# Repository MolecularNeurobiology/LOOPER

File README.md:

# LOOPER
Live Observation and Operation of Physiology Experiments with Robotics

# What is it?
LOOPER is an automated data collection platform for neonate pneumotachography experiments focused on the Autoresuscitation Reflex Assay. Its software is written in Python, and Arduino code (C++). The robotics includes commonly available electrical components, sensors, motors, and mechanical linkages. Structural components also include extruded aluminum pieces, 3D printed pieces, and milled acrylic. Physiology signals from laboratory grade sensors are captured using a LabJack analog to digital USB capture card connected to a Raspberry Pi Single Board Computer which provides access to the user interface. An Arduino Mega microcontroller with a custom assembled printed circuit board coordinates control of motorized parts.

Tools to aid in analysis of data collected with LOOPER are co-released at https://github.com/MolecularNeurobiology/Breathe_Easy

## What is the Autoresuscitation Reflex Assay? Why is it important?
The prevailing mechanistic hypothesis of Sudden Infant Death Syndrome/Sudden Unexpected Infant Death (SIDS/SUID) is that infants experience two critical failures that lead to death. The first is a failure of arousal. Many SIDS/SUID infants are found in an unsafe sleep environment, resulting in rebreathing increasingly hypoxic and hypercapnic air. Healthy infants arouse; however, in a vulnerable infant, the rebreathing continues, resulting in increasing levels of hypoxia and hypercapnia, leading to apnea and bradycardia. As a last line of defense, the infant initiates the **autoresuscitation reflex**. It is hypothesized that this second failure in the autoresuscitation reflex is a common mechanistic pathway for many SIDS cases. 

The neonatal mouse offers a powerful model for understanding intrinsic and extrinsic risk factors that may lead to failed autoresuscitation. Mouse neonate autoresuscitation parallels human cardiorespiratory physiology and can be readily assessed by subjecting a postnatal day 7-8 (P7-8) mouse to an anoxic gas mixture (3% CO2/97% N2) until apnea and bradycardia occur. Upon apnea, the neonate is returned to room air (approximately 21% O2/79%N2) to facilitate the autoresuscitation reflex and restore cardiorespiratory function. After a short recovery period, this sequence of events is repeated either for a predetermined number of trials or until the animal succumbs. 

However, the conventional autoresuscitation assay has several limitations that preclude wider use. First, the observer must be attentive throughout the assay to watch the cardiorespiratory traces in real-time, detect apnea, and provide room air rescue gas. This requirement for manual detection of cardiorespiratory signatures leads to inconsistency and inaccuracy. Second, an observer with one apparatus (pneumotachograph) can assay about three mice daily (~2.5 hours per assay). Given that mice must be P7-8, each litter is about eight pups, and each mating pair drops a litter once a month, it is impossible to record all mice, and there is a month’s downtime between experimental days. Ultimately, this culminates in wasted time and mice. Lastly, hand annotation and quantification of the data remain the standard in the field, creating an additional workload with the potential for observer bias. Altogether, these shortcomings create a high workload, low efficiency, and the potential for variability, severely limiting one of the most powerful assays for understanding SIDS mechanisms. 

While the **LOOPER** platform was created specifically to address experiments related to testing of the Autoresuscitation Reflex and SIDS/SUID, it provides an adaptable experimental framework that can be adapted to interrogate almost any aspect of neonatal cardiorespiratory function - making the platform useful for investigating a wide range of congenital or perinatal pathophysiologies (i.e. Rett Syndrome, Congenital Central Hypoventilation Syndrome, Neonatal Opioid Withdrawal Syndrome).

The **LOOPER** platform and accompanying data analysis tools from [BREATHE_EASY](https://github.com/MolecularNeurobiology/Breathe_Easy) now enable the automation of the assay and scaling of testing capacity, allowing a single investigator to test full litters of mice.

Figure 1. The role of autoresuscitation in SIDS and how automation improves testing that outcome in rodent models. (A) Schematic representation of the leading hypothesis behind the role of failed autoresuscitation in SIDS or SUID deaths. Numbers throughout the graphic indicate the numerical order in which the marked physiological events occur, and they also correspond to the estimated level of oxygen and carbon dioxide in the infant in the line graph on the lower center. This line graph is a figurative model and does not represent real data. (B) An example of a successful autoresuscitation response was measured in a laboratory mouse, and each critical physiological event was marked with bolded text. Additionally, we have highlighted some of the measurable outcomes from those physiological events in italicized text, which can be used to understand the dynamics of the response. Respiratory parameters are highlighted with maroon coloring, whereas cardiovascular parameters are highlighted in dark forest green. (C) A graphic demonstrating the required human interaction time for manual performance of this assay in lab rodents, as highlighted with the maroon hand with an eye. The "hand with eye" represents that a human must interact with the system and continue paying attention to perform interventions throughout this process. In contrast, our LOOPER system automates six of the eight steps, as demonstrated with the teal gear symbol, which reduces the required human interaction time by 98%. (D) Updates for the Breathe_Easy platform enable automation of data analysis for data generated on the LOOPER platform.

# Main Features
What does LOOPER do?

1. Real-time data collection using a LabJack analog to digital interface
1. Real-time detection of breathing and heartbeat
1. Automated closed-loop control of experiment steps via communications with an Arduino microcontroller and robotics components
1. Calibration air injections with a robotically actuated micropipette
1. Initiation of gas challenges with valve controls and motorized placement of gas exposure outlets
1. Identification of sustained apnea
1. Automated transition back to room air
1. Automated detection of cardio-respiratory recovery
1. Repetition autoresuscitation challenges

# Where to get it? How to build it? How to use it?
The software (available as source code), [build instructions](https://molecularneurobiology.github.io/LOOPER/doc/build/html/index.html) (including parts lists and schematics), and [user manual](https://molecularneurobiology.github.io/LOOPER/User_Manual/build/html/index.html) for conducting an Autoresuscitation Assay are available at our project repository for [LOOPER](https://github.com/molecularneurobiology/LOOPER).

## Where is the build manual?
Access the build guide for the robotics components [here](https://molecularneurobiology.github.io/LOOPER/doc/build/html/index.html). This provides parts lists of commercially available parts, fabrication instructions and specifications for custom 3D printed, milled, or PCB components, and an assembly and set-up guide.

## How do I set up the user interface software?
### Dependencies
The environment needed to run LOOPER can be created using a Python virtual environment tool (such as miniforge). A requirements.txt and pyproject.toml file enumerate the Python packages and versions that are suggested. Arduino code needed for flashing the microcontroller is available in the ArduinoCode subfolder

#### Installation and Usage - Python component
##### Install Python3
Download Python [here](https://www.python.org/downloads/)
or https://conda-forge.org/download/

##### Install Python Dependencies
Activate Python virtual environment to help manage package installation.
```
# Posix
python3 -m venv <venv>
source <venv>/bin/activate
```

Install dependencies
```
pip install -r requirements.txt
```

##### Running From Source
```
# Posix
source venv/bin/activate
python3 PCC.py
```

## How do I use LOOPER to perform an Autoresuscitation Assay?
Our user guide for interacting with the LOOPER system and its user interface is available [here](https://molecularneurobiology.github.io/LOOPER/User_Manual/build/html/index.html).

# Licensing
'LOOPER' is dually licensed. The project is available under a 'GPLv3 or later' license as well as a commercial license (inquiries for commercial licensing may be directed to Russell.Ray@bcm.edu). 

    LOOPER - Live Observation and Operation of Physiology Experiments with Robotics
    Copyright (C) 2019  
    Christopher Ward, Nicoletta Memos, Savannah Lusk,
    Mariana Garcia Costa, Wenyu Zuo, Eunice Aissi, Brandon Ruiz, 
    Dipak Patel, Kevin Jiang, Andersen Chang, and Russell Ray.

    This program is free software: you can redistribute it and/or modify
    it under the terms of the GNU General Public License as published by
    the Free Software Foundation, either version 3 of the License, or
    any later version.

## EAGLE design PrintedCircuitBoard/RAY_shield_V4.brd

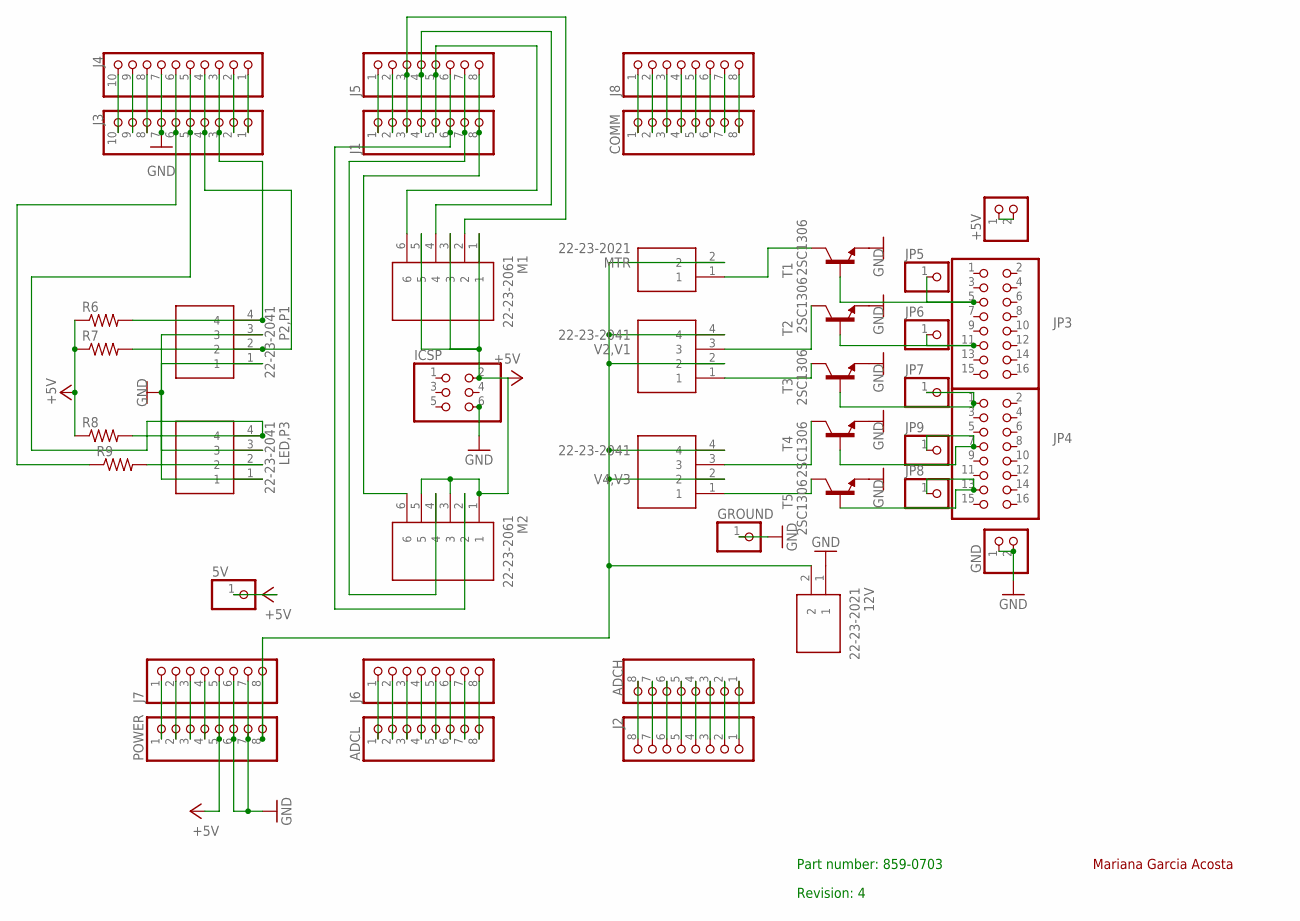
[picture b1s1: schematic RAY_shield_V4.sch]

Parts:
5V: PINHD-1X1; 1X01
12V: 22-23-2021; SHDR2W87P0X254_1X2_493X635X110
+5V: PINHD-1X2; 1X02
ADCH: PINHD-1X8TH; 1X08-TH
ADCL: PINHD-1X8TH; 1X08-TH
COMM: PINHD-1X8TH; 1X08-TH
GND: PINHD-1X2; 1X02
GROUND: PINHD-1X1; 1X01
ICSP: PINHD-2X3; 2X03
J1, J2, J5, J6, J7, J8: PINHD-1X8TH; 1X08-TH
J3, J4: PINHD-1X10TH; 1X10-TH
JP3, JP4: PINHD-2X8; 2X08
JP5, JP6, JP7, JP8, JP9: PINHD-1X1; 1X01
LED,P3: 22-23-2041; SHDR4W87P0X254_1X4_1001X635X11
M1, M2: 22-23-2061; SHDR6W87P0X254_1X6_1509X635X11
MTR: 22-23-2021; SHDR2W87P0X254_1X2_493X635X110
P2,P1: 22-23-2041; SHDR4W87P0X254_1X4_1001X635X11
POWER: PINHD-1X8TH; 1X08-TH
R6, R7, R8, R9: R-US_0207/7; 0207/7
T1, T2, T3, T4, T5: 2SC1306; TO220BV
V2,V1, V4,V3: 22-23-2041; SHDR4W87P0X254_1X4_1001X635X11

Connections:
+5V: 5V.1, ICSP.2, J7.5, M1.1, M1.3, M1.5, M2.1, M2.3, M2.5, POWER.5, R6.1, R7.1, R8.1
+12V: 12V.2, J7.8, MTR.2, POWER.8, V2,V1.2, V2,V1.4, V4,V3.2, V4,V3.4
GND: 12V.1, GND.1, GND.2, GROUND.1, ICSP.6, J3.7, J4.7, J7.6, J7.7, LED,P3.1, LED,P3.3, P2,P1.1, P2,P1.3, POWER.6, POWER.7, T1.3 (E), T2.3 (E), T3.3 (E), T4.3 (E), T5.3 (E)
unnamed: +5V.1, +5V.2
unnamed: J3.1, J4.1
unnamed: J3.6, J4.6, R9.1
unnamed: JP3.5, JP5.1, T1.1 (B)
unnamed: J3.4, J4.4, P2,P1.2, R7.2
unnamed: J3.2, J4.2
unnamed: J3.3, J4.3, P2,P1.4, R6.2
unnamed: J1.1, J5.1
unnamed: J1.2, J5.2
unnamed: J1.3, J5.3, M1.2
unnamed: J1.4, J5.4, M1.4
unnamed: J1.5, J5.5, M1.6
unnamed: J1.6, J5.6, M2.2
unnamed: J1.7, J5.7, M2.4
unnamed: J1.8, J5.8, M2.6
unnamed: JP3.11, JP6.1, T2.1 (B)
unnamed: JP4.7, JP9.1, T4.1 (B)
unnamed: ADCL.1, J6.1
unnamed: ADCL.2, J6.2
unnamed: ADCL.3, J6.3
unnamed: ADCL.4, J6.4
unnamed: ADCL.5, J6.5
unnamed: ADCL.6, J6.6
unnamed: JP4.1, JP7.1, T3.1 (B)
unnamed: JP4.13, JP8.1, T5.1 (B)
unnamed: MTR.1, T1.2 (C)
unnamed: T2.2 (C), V2,V1.3
unnamed: T3.2 (C), V2,V1.1
unnamed: T4.2 (C), V4,V3.3
unnamed: T5.2 (C), V4,V3.1
unnamed: LED,P3.2, R9.2
unnamed: ADCL.7, J6.7
unnamed: ADCL.8, J6.8
unnamed: ADCH.1, J2.1
unnamed: ADCH.2, J2.2
unnamed: ADCH.3, J2.3
unnamed: ADCH.4, J2.4
unnamed: ADCH.5, J2.5
unnamed: ADCH.6, J2.6
unnamed: J7.4, POWER.4
unnamed: J3.9, J4.9
unnamed: ADCH.7, J2.7
unnamed: ADCH.8, J2.8
unnamed: COMM.1, J8.1
unnamed: COMM.2, J8.2
unnamed: COMM.3, J8.3
unnamed: COMM.4, J8.4
unnamed: COMM.5, J8.5
unnamed: COMM.6, J8.6
unnamed: COMM.7, J8.7
unnamed: COMM.8, J8.8
unnamed: J3.5, J4.5, LED,P3.4, R8.2
unnamed: J7.2, POWER.2
unnamed: J7.1, POWER.1
unnamed: J3.8, J4.8
unnamed: J3.10, J4.10
RESET: J7.3, POWER.3

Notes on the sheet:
Mariana Garcia Acosta
Part number: 859-0703
Revision: 4

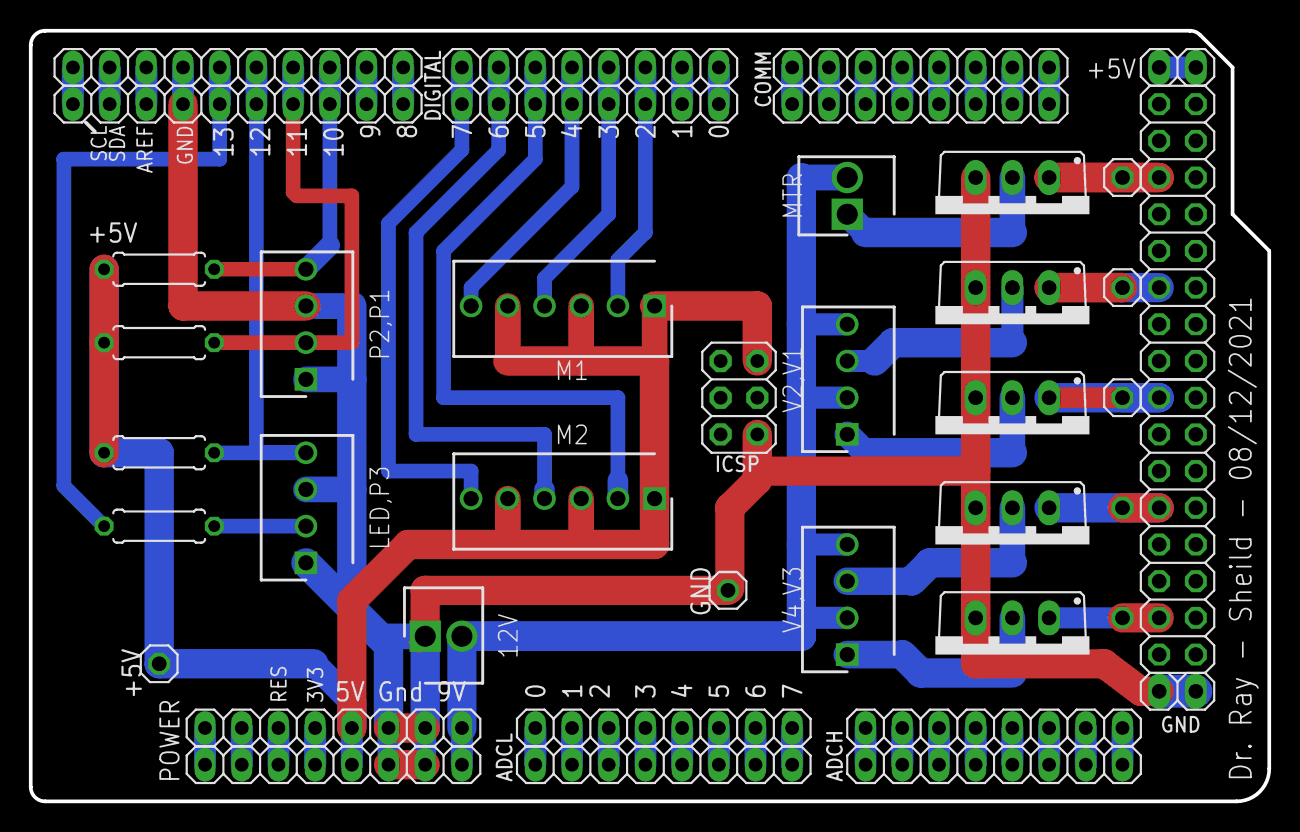
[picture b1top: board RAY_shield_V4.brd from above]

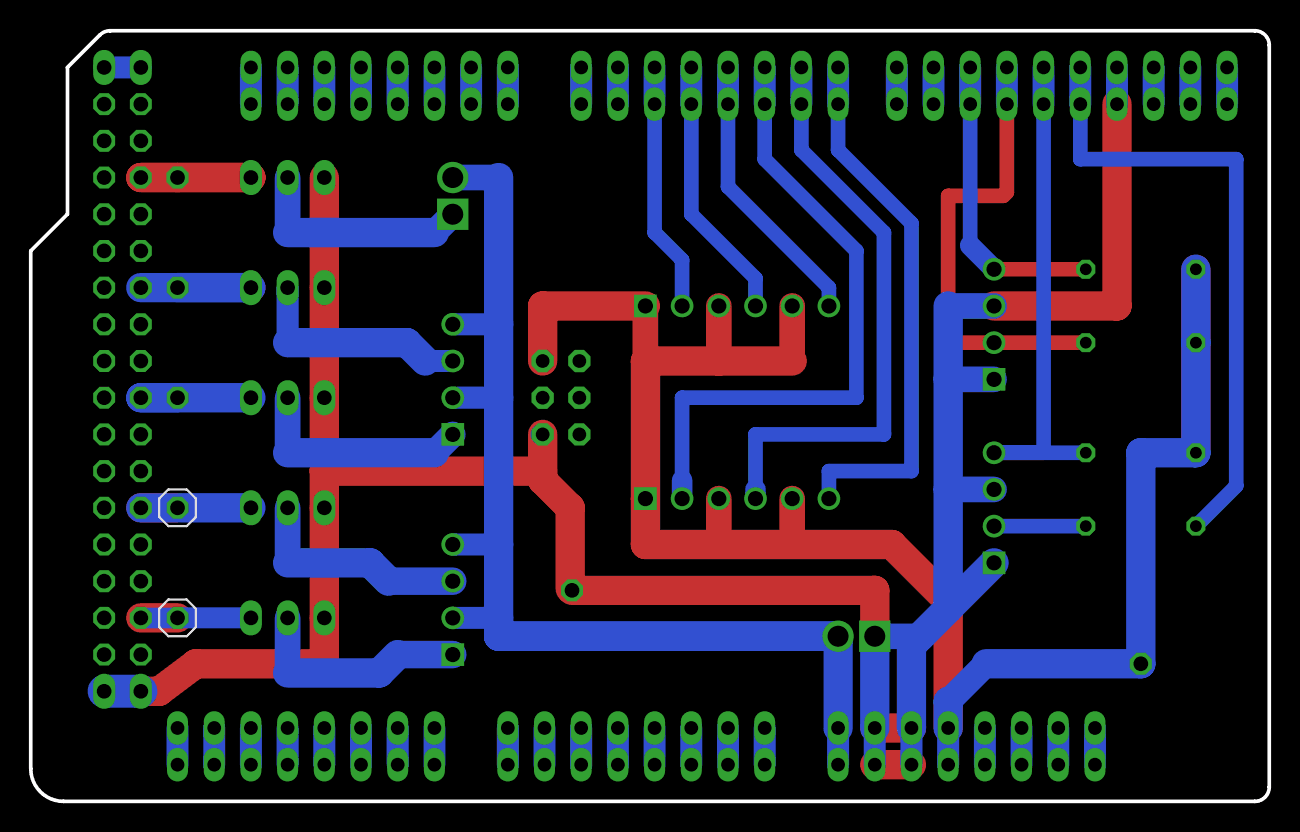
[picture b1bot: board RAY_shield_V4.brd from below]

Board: 2 copper layers, 85.7 x 53.3 mm, 41 parts (2 on the bottom side), 60 nets.

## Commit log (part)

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2022-01-27 create license
    created restricted license
2022-01-27 Initial commit using v40, minor updates removing dead code, update to header, new verion incremented to 41.0.1
2022-01-31 Add files via upload
    original and updated Arduino code
2022-02-02 dev branch creation for next revision to PCC
2022-02-02 relaxed 'save lock'
2022-02-02 fixed typo in setting default Mode_Dict
2022-02-02 added additional contributor to project
2022-02-02 added tasks as part of release-002 changes to PCC
2022-02-03 minor edit to PCC_output_exporter.py
2022-02-11 basic logging setup
2022-02-11 labjack reset added, gpio workaround for no RPi testing
    added code to test if labjack stream left running due to bad exit and reset if needed, added try/excpt to handle gpiozero error when testing code on non-RPi system
2022-02-11 created logging for console and file
2022-02-11 update to PCC output exporter to provide labchart friendly output
2022-02-15 fix for co2 timer
2022-02-19 revert to prior release-001 version
    release-001 was accidentally updated - this should revert back to the release-001 version
2022-02-21 added habituation-1 and 2 to savable modes
2022-02-23 Remove .DS_Store from everywhere
2022-02-23 mqtt test and gui fix
2022-02-24 fix for files unable to process due to disrupted row - likely timing conflict with arduino and labjack comms
2022-02-25 Add files via upload
    updated arduino code with condensed serial.print commands
2022-02-28 gui pulled out and mqtt test2
2022-03-01 cleaned up
2022-03-01 deleted old c code
2022-03-01 server file - example for manager worker i/o
2022-03-07 no more mqtt
2022-03-07 demo test
2022-04-08 back to working
2022-06-03 updated minimum sustained recovery logic
    needed to account for possibility of sustained recovery equaling its limit.
2022-07-19 update to PCC_output_exporter, issue #29
2022-08-25 permit manual set of baseline BPM and HR - retry
2022-08-25 update to GEMouse, v1.0.0 feature complete ready for testing
2022-08-26 updated GEMouse v1.0.1 QOL and bugfixes applied
2022-08-26 PCC, addition of gasp and recovery detection, alternate recovery modes
2022-08-27 bugfixes from on rig testing
    extended baseline seems to work (though gui not sure if gui counter of QB duration is accurate or overcounting?)
    alternative recovery detection appears to work
    expanded logging of gasp and recovery seem to work
    GEMouse troubleshooting for Raspberry Pi QT (color response and RPi pin in/out), main features appear complete. additional feature to skip and revert state in a cycle program would be a good future a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
2022-09-27 draft version of SHAM functional
    ready for feedback and additional testing. current limit appears to be the HR detection, revision to ECG analyzer likely needed - redo file add
2022-09-28 update to SHAM.py header
2022-09-30 fix to bug in recovery detection
2022-10-02 in progress draft of Teace_Viewer
2022-10-03 basic graphing features added
    need to finish implementation of additional graph selections, need to add navigation tools (scan along by time, jump to timestamp)
2022-10-05 annotation tools feature complete
    still work to do for 'jumping to sections tools' and other enhanced features
2022-10-06 updated feature notes
2023-03-08 1st draft gui for ccac tool (#52)
2023-03-08 added toolbar functionality (#53)
2023-05-18 update to ccac_tools
    added retry capability and testing to ensure original and copy location are different before deletion can occur
2023-08-26 added crawl and compare tool to the ccac_tools
2023-10-03 updated default test parameters
2023-10-24 fixed bug - failed copies requiring retry would report as successful in end of run report
    needed to fix how the True/False result was being returned, lists with values evaluate as True, needed to return a bare result
2023-12-13 Update CONSTANTS.py
    Changed SLB_Trigger value from 5 to 7
2024-01-09 Updated arduino code and added PCB code.
2024-01-09 Added PCC GUI development images and notes.
2024-02-15 added pin reading display feature to troubleshoot gemouse
2024-02-15 update to default settings of beat_caller to match those currently implemented in the 3.12 compatible SASSI with the new beatcaller
2024-02-15 updates for trying new beat_caller function for real_time
    testing on rig still needed
2024-02-21 Update PCC.py
    doofus,... peak_finding_distance not minRR in find_peaks
2024-03-04 fm api testing
2024-03-04 added template for rig config
2024-03-04 scan to save feature ready to test
2024-03-06 Rsync.sh
    Code that is currently on the Rig's
2024-04-09 mods to readme and addition of schema for command center and refactor
2024-04-18 draft, additions for fm-write
2024-05-07 bugfix for number on rig, added rig_clean_up script
2024-06-26 bugfix rig_clean_up
2024-07-30 bugfix to avoid searching 'hidden folders'
2024-10-04 added module for loading and saving settings
2024-10-28 implementation of sim_mode
2024-11-25 pruning of stale files, not in use
2024-12-06 bugfix for rig_clean_up.py. filter fm returns by delete status
2024-12-08 resize last and longest co2 boxes
2024-12-09 Create doc folder
2024-12-09 Create blank
2024-12-13 starting point for expanding client
2024-12-14 implementing basic i/o
    basic i/o and connection with minerva plugin and simulated signals
2024-12-15 modified legend placement
2024-12-17 add kill command line argument and other things
    also added folders to stage development on docker and ansible development, updated STREAMS to include arduino finding feature
2025-01-25 starting implementation of STAGES progression
2025-01-30 minerva integration testing
2025-02-11 bugfix for deleterecord using lowercase yes
2025-04-05 bugfix for mp related hang on exit
2025-04-09 added tracking of lag, integration with fm_tools, placeholder for file saving
2025-04-30 wip updates
2025-04-30 created pyproject.toml
2025-05-01 raspi testing
2025-05-02 raspi arduino comtest
2025-05-10 added logging of unknown commands
2025-05-16 Fix typo
2025-05-29 payload wip - payload preview in debug log
2025-05-29 downgraded ping log event to debug instead of info
2025-06-01 feat: streaming first pass
2025-06-06 bugfix for arduino byte string parsing, tweaks to stage end detection, bugfix for baseline calm detection
2025-06-11 fm related script testing
2025-06-11 added challenge duration history
2025-06-11 Add True flag to plugin
2025-06-18 version increment
2025-06-24 feature implemented and notes added
2025-06-24 add argparse for testing mode of fm_reporting
2025-06-24 add hello_world.py
2025-06-24 updated h_w.py
2025-06-24 inclusion of fm_reporting.bat example
2025-06-26 add pcc version infor to file output
2025-06-27 seperated lj and arduino sim settings
2025-06-27 arduino integration testing
2025-06-30 update email text to reflect friday schedule
2025-06-30 bugfix, case sensitive arduino commands
2025-07-02 add pyproject.toml revised for compatibility
2025-07-02 added 4 arduino quick command buttons
2025-07-14 pyside6 compat for gemouse, pi5 gpio compat
2025-07-18 update to reporting format
2025-07-18 update to graphing
2025-07-22 fix queue initalization
2025-07-23 disabled, commented out some debug printing/logging
2025-07-23 added quick arduino calibration buttons
2025-07-28 tweak colors for arduino quick cal buttons
2025-07-29 Configures stream control queue with TTL and max length
    Ensures that the stream control queue, used for heartbeat
    commands, respects the TTL and max length configurations
    defined in the API. This prevents the queue from growing
    unboundedly and ensures timely processing of control
    messages.
2025-07-29 Filters None values in timestamp data
    Ensures only valid numeric timestamp values are used
    when generating timestamp signal data.
    This prevents potential errors and unexpected behavior
    caused by None or non-numeric values during data
    processing.
2025-08-06 remove lgpio from toml, set logger to null at beginning of PCC
2025-08-06 populate minervaplugin congig.py ip address for testing server ip
2025-08-07 add shell template for running GEMouse.py
2025-08-07 bugfix
2025-08-07 bugfix beat_caller index out of range due to bad downsample still present in TS variable
2025-08-07 remove print call in beat_caller
2025-08-07 increment version prepare tag
2025-08-11 dev_2025-08-11a
    dev_2025-08-11a
2025-08-11 updated data for payload
2025-08-14 button fixes for arduino testing
2025-08-15 Adds comprehensive status reporting
    Implements a centralized status reporting system for the plugin.
    This system provides structured status reporting with severity levels, categorization, deduplication, and automatic retention management. It allows different components to report statuses, which are 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
2025-08-15 MinervaPlugin: dynamic command passthrough; remove tests dependent on Start step transforms; add PCC dispatcher example; simulator: string-based dispatch
2025-08-15 Add PCC integration comments in PCC.py and integration notes for dynamic commands
2025-08-18 bugfix for challenge recovery detect, and baseline quality timer starting negative
2025-08-18 Update pyproject.toml
    fix typo in email
2025-08-19 implemented stage declaration of payload data
2025-08-19 Adds duration signal type
    Adds a duration signal type with duration and severity levels to the Minerva plugin.
    This enhancement allows the simulation to send duration-based signals with associated severity, providing more detailed information on the state of the simulated system. Includes example duration sig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
2025-08-19 Adds Minerva Plugin API documentation
    Provides a comprehensive README file detailing the Minerva Plugin API, including data classes, public methods, intended use cases, and architectural notes, enabling developers to effectively integrat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
2025-08-22 bugfixes for changes to command payloads - still wip
2025-08-23 bugfix to enable rabbitmq connection
2025-08-28 Fix payload generation
    Adds dynamic rate control to the streaming system based on client performance metrics. This helps to optimize the streaming experience by adjusting the streaming rate in response to client-side rende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
    Also includes enhancements to time series data handling in the data payload, incorporating dynamic time window calculations with padding for improved visualization. A fallback mechanis
2025-08-28 wip update to email
2025-08-30 draft implementation of ansible for rig management
2025-09-03 error reporting email inclusion of usable stats
2025-09-08 screenshots for legacy PCC added
2025-09-10 Downsamples time series data for streams
    Reduces stream payload size by downsampling time series data.
    This change implements a downsampling method that averages data points within a dynamically calculated window, reducing the number of points sent while preserving signal fidelity. Configurable target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
    This reduces the amount of transmitted data per stream, improving responsiveness and performance.
2025-09-12 Improves command processing and RabbitMQ connection
    Prioritizes critical commands by placing them at the front of the queue for immediate execution.
    Optimizes RabbitMQ connection parameters and message consumption, particularly for Windows environments, to prevent blocking. This includes reducing timeouts, adding connection retries, and implement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
    Adjusts stream configuration TTL and user timeout values.
2025-09-17 Improves plugin performance and stability
    Addresses performance bottlenecks and stability issues within the plugin.
    - Implements adaptive streaming rate control based on command
    processing time to prevent resource exhaustion. Adjusts the
    streaming rate dynamically, reducing it when commands take longer
    to process and increasing it when commands are processed quickly.
    - Introduces a dedicated command consumer with a separate connection
2025-10-01 latest code with ball housing fixed
2025-10-14 prepare for settings loading from FM
2025-10-21 Revert "Dev"
2025-11-23 added ansible folder
2025-12-19 web doc cross linking
2025-12-19 save doc update
2025-12-22 updates for setting up new rigs
2025-12-22 rsync
2025-12-22 fix for git clean
2025-12-23 name tweaks
2026-01-02 Update User_Manual.html
    missing closing parenthesis
2026-01-12 new baseline vf cutoff
2026-01-13 revised tag
2026-01-23 adding links to readme
2026-01-23 User Manual Update
